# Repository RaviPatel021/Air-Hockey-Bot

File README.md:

# Autonomous Air Hockey Table

This repository contains all the code and hardware files for an autonomous air hockey table system. The system uses a 2-axis gantry controlled by an ESP32, with real-time vision and inference running on either a laptop or a Jetson Nano.

## Folder Overview

- **embedded/**  
  Contains the embedded C++ code for the ESP32 that controls the 2-axis gantry using stepper motors and drivers.

- **laptop/**  
  Python code that runs on a laptop to handle camera input, detect the puck, run inference using a trained model, and send paddle commands to the ESP32 over serial.

- **Jetson_Nano/**  
  Similar to the `laptop/` folder, but modified and optimized to run entirely on a Jetson Nano for a fully embedded setup.

- **KiCAD_Schematics/**  
  Electrical schematics and PCB layout files for the gantry control system, designed using KiCAD.

---

More detailed documentation and setup instructions will be added soon.

## 🚀 Getting Started

These instructions will help you get the system running on your machine.

### 1. Clone the Repository

```bash
git clone https://github.com/RaviPatel021/Air-Hockey-Bot.git
cd Air-Hockey-Bot
````

### 2. Install Python Dependencies

Use Python 3.8–3.10. It's strongly recommended to use a virtual environment:

```bash
python -m venv venv
venv\Scripts\activate  # Mac/Linux:: source venv/bin/activate
pip install -r laptop/requirements.txt
```

> ⚠️ On Jetson Nano, some packages (e.g., OpenCV, torch) may need to be installed with Jetson-specific wheels

---

## 🔧 Upload Firmware to ESP32

The ESP32 controls the stepper motors through UART and must be flashed with the code in `embedded/`.

You can upload the code using:

* **Arduino IDE** (select ESP32 board, e.g. “ESP32 Dev Module”)

Make sure you have the required libraries installed:

* TMCStepper
* FastAccelStepper

---

## ⚙️ Connect the System

1. Connect the camera and ESP32 to your computer or Jetson Nano.
2. Verify the serial port device (e.g., `/dev/ttyUSB0` on Linux or `COM3` on Windows).
3. Adjust serial port settings in the Python code if necessary.

---

## ▶️ Running the Control Script

From the `laptop/` or `Jetson_Nano/` directory, run:

```bash
python main.py
```

This will start the vision processing pipeline, detect the puck position, run the PPO model inference, and send velocity commands to the gantry controller.

---

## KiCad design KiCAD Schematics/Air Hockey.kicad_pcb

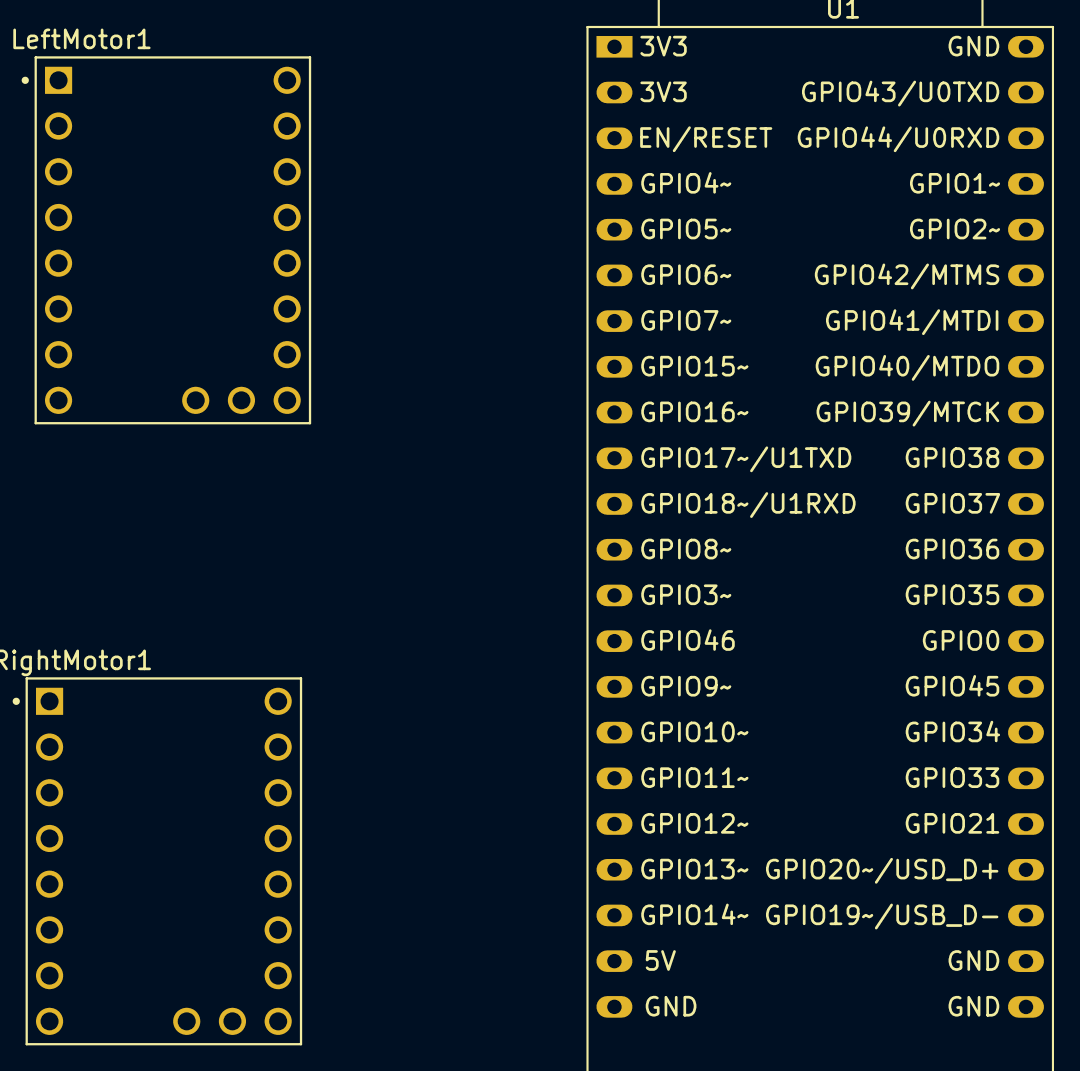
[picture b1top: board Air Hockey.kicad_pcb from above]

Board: 2 copper layers, 3 parts (0 on the bottom side), 11 nets, no tracks yet.

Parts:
LeftMotor1: TMC2209_BigTreeTech_V1.3; MODULE_TMC2209_SILENTSTEPSTICK
RightMotor1: TMC2209_BigTreeTech_V1.3; MODULE_TMC2209_SILENTSTEPSTICK
U1: ESP32-S2-DevKitC-1

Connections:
unnamed: LeftMotor1.7 (GND), RightMotor1.7 (GND)
unnamed: LeftMotor1.9 (DIR), U1.6 (GPIO6/ADC1_CH5)
unnamed: LeftMotor1.1 (GND), LeftMotor1.14 (MS2), LeftMotor1.15 (MS1), RightMotor1.1 (GND), RightMotor1.14 (MS2), RightMotor1.15 (MS1), U1.22 (GND)
unnamed: LeftMotor1.13 (RX), RightMotor1.13 (RX), U1.10 (GPIO17/ADC2_CH6/U1TXD)
unnamed: LeftMotor1.10 (STEP), U1.5 (GPIO5/ADC1_CH4)
unnamed: LeftMotor1.2 (VIO), RightMotor1.2 (VIO), U1.2 (3V3)
unnamed: LeftMotor1.8 (VS), RightMotor1.8 (VS)
unnamed: LeftMotor1.16 (~EN), U1.4 (GPIO4/ADC1_CH3)
unnamed: RightMotor1.9 (DIR), U1.9 (GPIO16/ADC2_CH5/32K_N)
unnamed: RightMotor1.10 (STEP), U1.8 (GPIO15/ADC2_CH4/32K_P)
unnamed: RightMotor1.16 (~EN), U1.7 (GPIO7/ADC1_CH6)

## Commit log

2024-10-07 Added second table
2024-10-09 Clean repo and added readme and requirements
2024-10-09 changed the control
2024-10-09 fixed controls
2024-10-14 Collisions solved
2024-10-14 Observation function added
2025-06-09 Added Code and Circuit Schematics
2025-06-09 Added Readme
2025-06-09 Cleaned up code
